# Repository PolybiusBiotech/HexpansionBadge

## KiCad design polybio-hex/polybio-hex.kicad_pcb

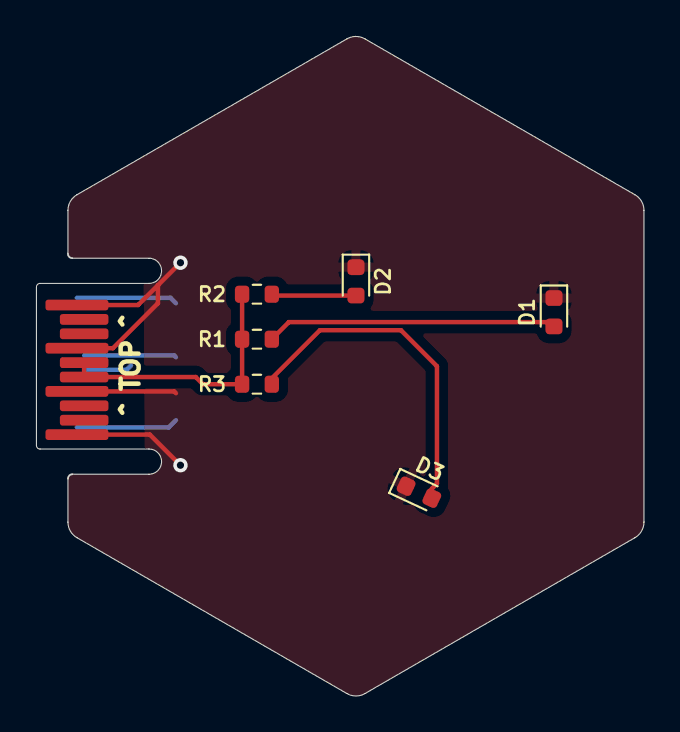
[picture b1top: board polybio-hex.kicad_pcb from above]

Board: 2 copper layers, 33.7 x 36.6 mm, 7 parts (0 on the bottom side), 5 nets.

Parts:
D1, D2, D3: LED; LED_0603_1608Metric
J1: Hexpansion-Connector; hexpansion-edge-connector
R1, R2, R3: R; R_0603_1608Metric

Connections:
/3V3: J1.15 (3V3), J1.16 (3V3), R1.1, R2.1, R3.1
/GND: D1.1 (K), D2.1 (K), D3.1 (K), J1.1 (GND), J1.6 (HEXP_DET), J1.10 (GND), J1.11 (GND), J1.14 (GND), J1.17 (GND), J1.20 (GND)
unnamed: D1.2 (A), R1.2
unnamed: D2.2 (A), R2.2
unnamed: D3.2 (A), R3.2

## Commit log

2024-04-22 First commit of first pass
